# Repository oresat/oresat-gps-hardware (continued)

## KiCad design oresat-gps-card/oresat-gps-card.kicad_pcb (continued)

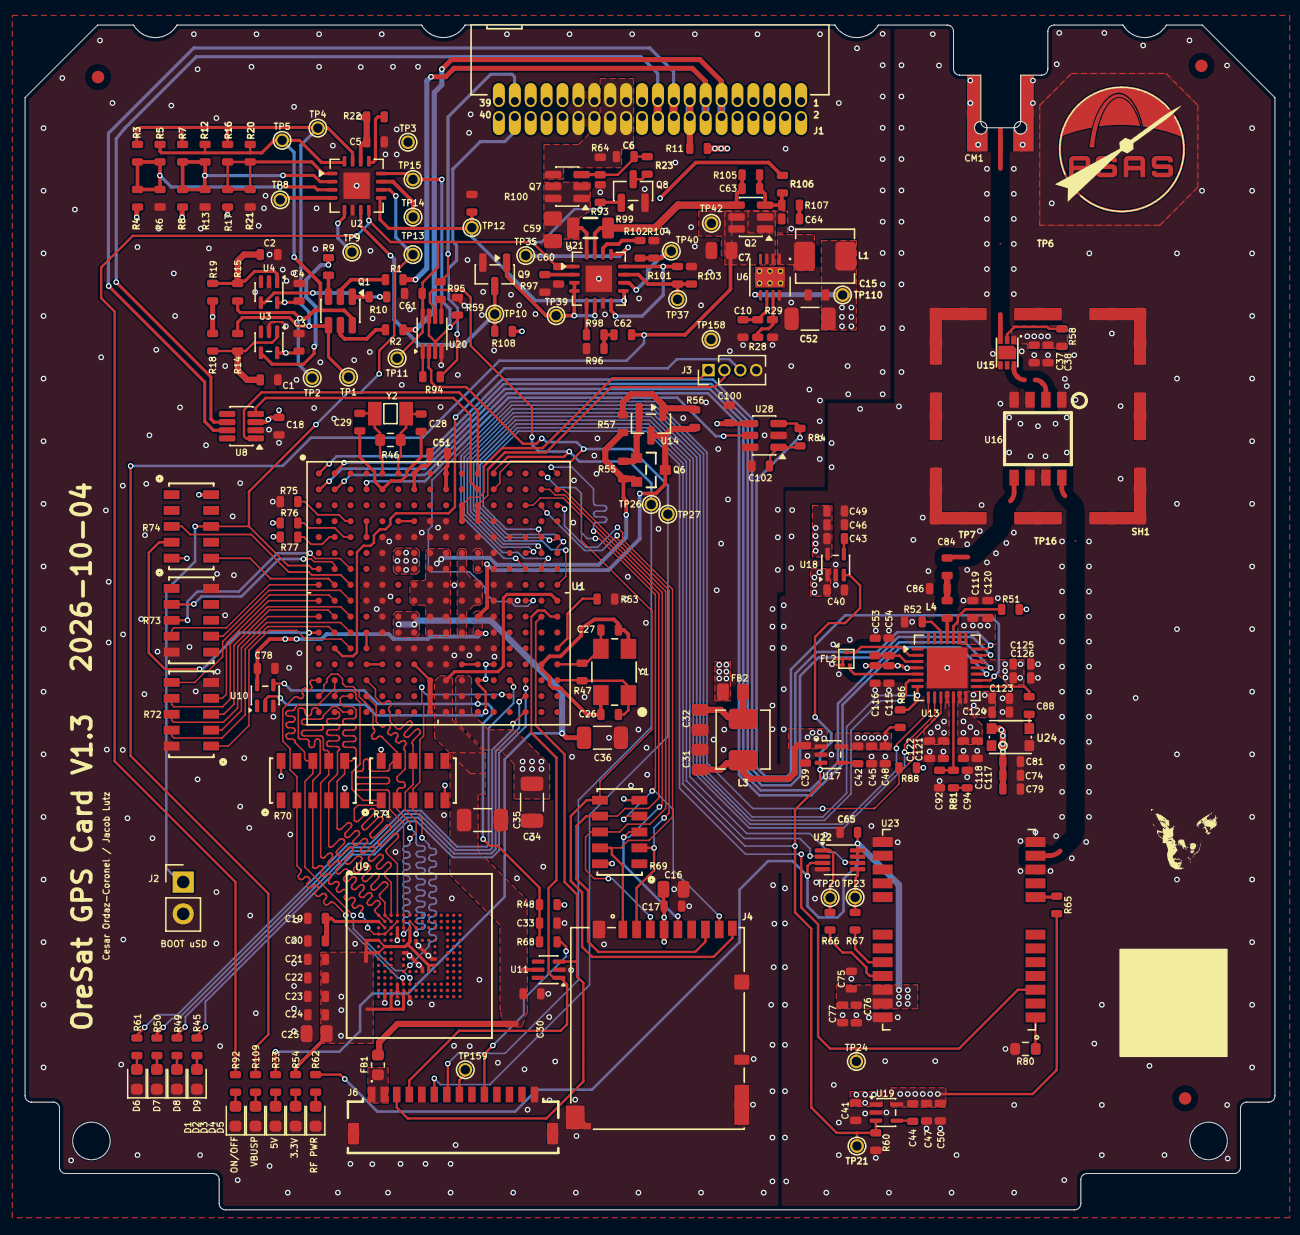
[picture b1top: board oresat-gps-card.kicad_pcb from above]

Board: 4 copper layers, 99.8 x 94.6 mm, 249 parts (0 on the bottom side), 188 nets.

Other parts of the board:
LOGO1: PSAS_LOGO_10X10

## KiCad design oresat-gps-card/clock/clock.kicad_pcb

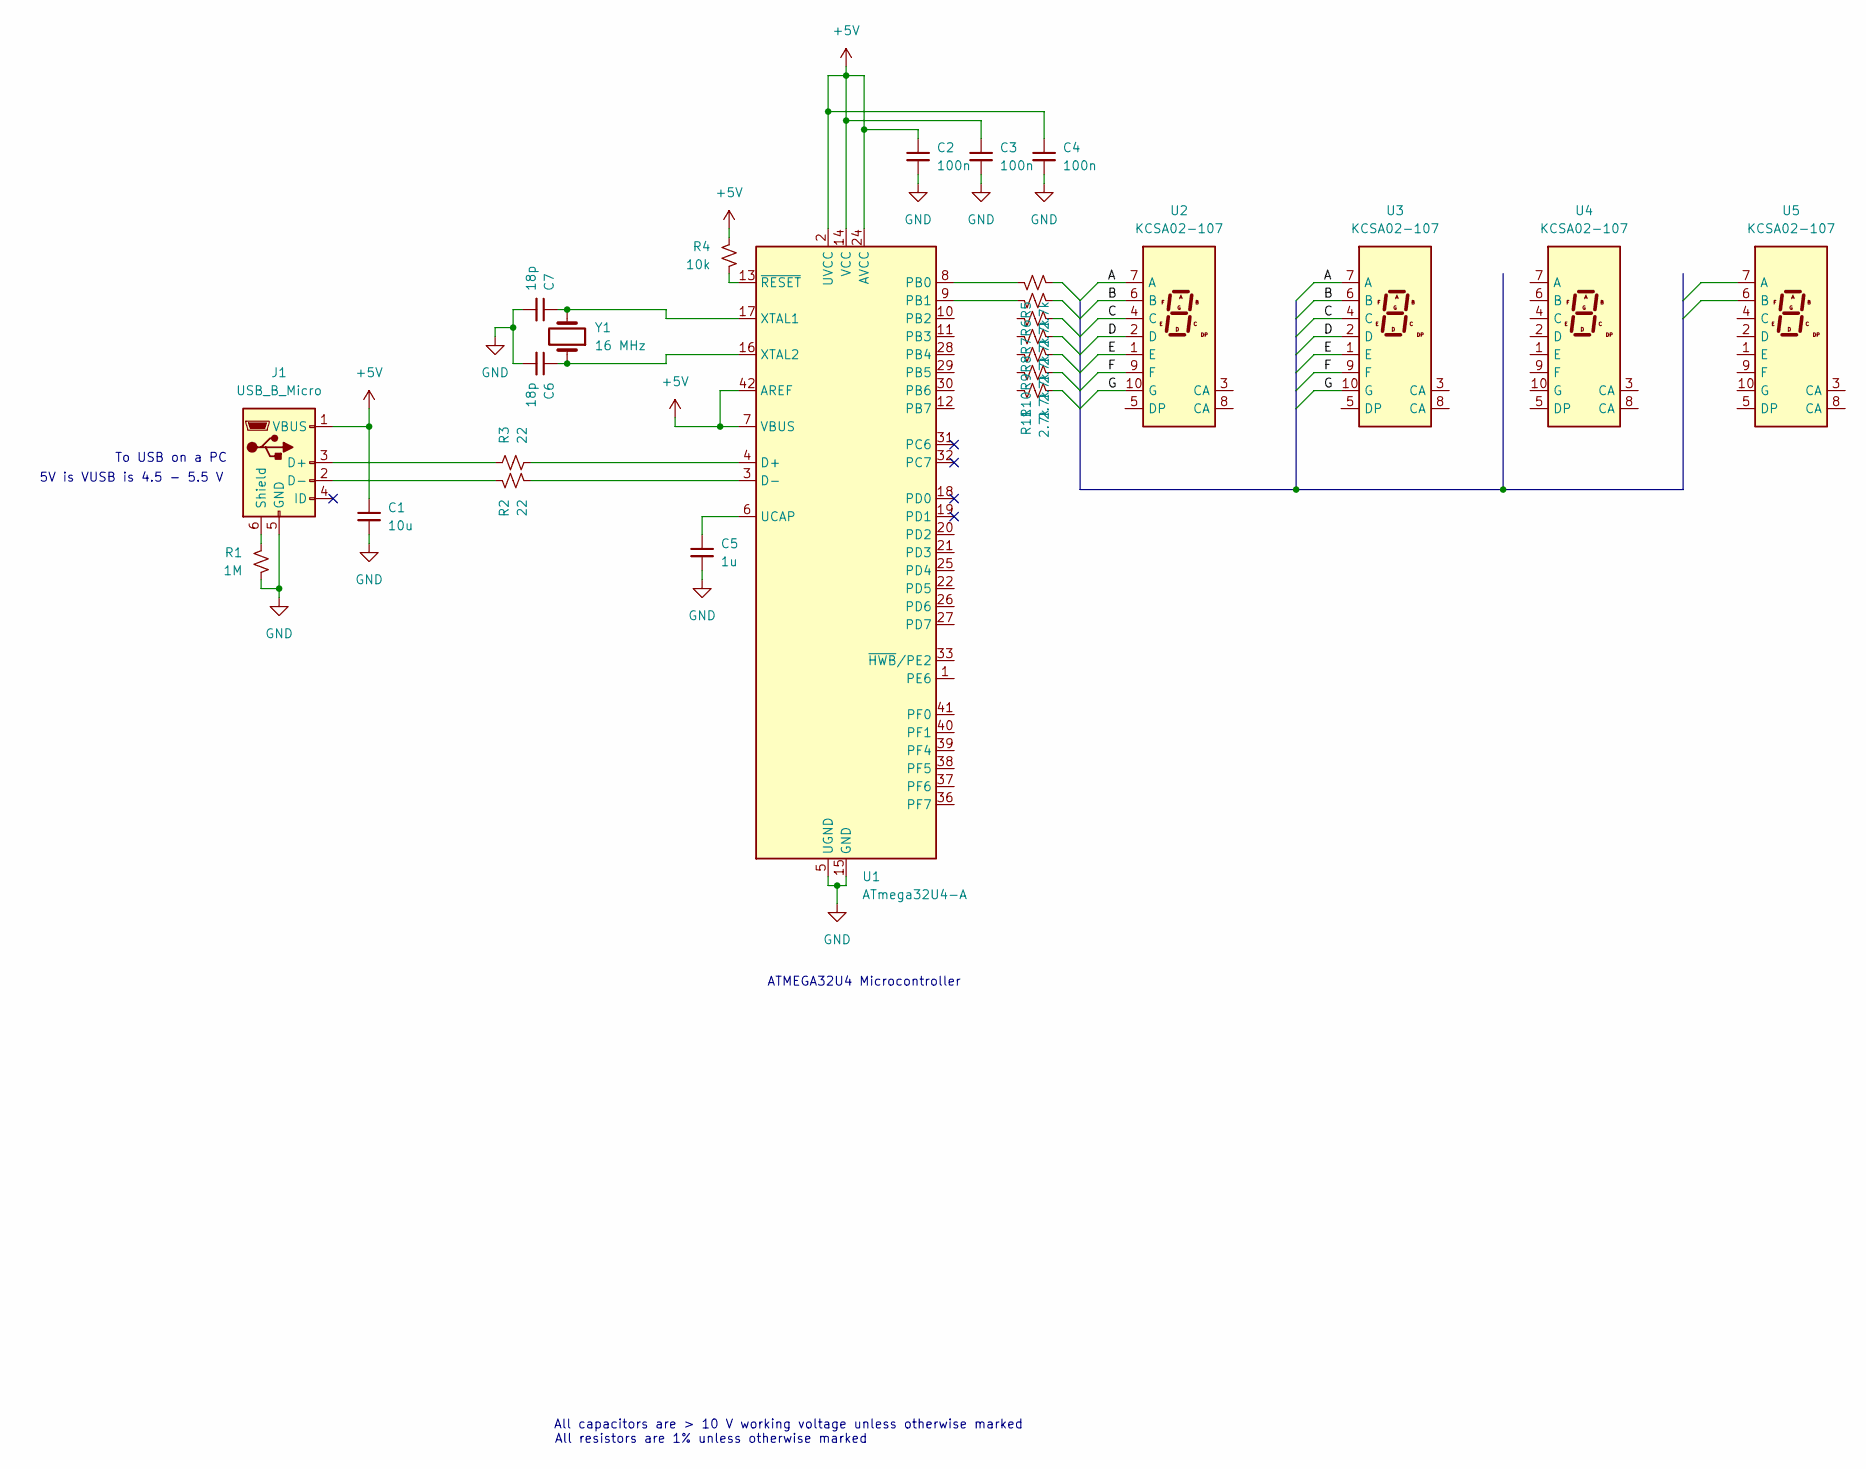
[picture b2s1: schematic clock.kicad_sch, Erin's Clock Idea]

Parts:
C1: 10u; C_0805_2012Metric
C2, C3, C4: 100n; C_0805_2012Metric
C5: 1u; C_0805_2012Metric
C6, C7: 18p; C_0805_2012Metric
J1: USB_B_Micro; USB_Micro-B_GCT_USB3076-30-A
R1: 1M; R_0805_2012Metric
R2, R3: 22; R_0805_2012Metric
R4: 10k; R_0805_2012Metric
R5, R6, R7, R8, R9, R10, R11: 2.7k; R_0805_2012Metric
U1: ATmega32U4-A; TQFP-44_10x10mm_P0.8mm
U2, U3, U4, U5: KCSA02-107; KCSC02-107
Y1: 16 MHz; Crystal_SMD_2012-2Pin_2.0x1.2mm

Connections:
+5V: C1.1, C2.1, C3.1, C4.1, J1.1 (VBUS), R4.1, U1.2 (UVCC), U1.7 (VBUS), U1.14 (VCC), U1.24 (AVCC), U1.34 (VCC), U1.42 (AREF), U1.44 (AVCC)
/A: U2.7 (A), U3.7 (A)
/B: U2.6 (B), U3.6 (B)
/C: U2.4 (C), U3.4 (C)
/D: U2.2 (D), U3.2 (D)
/E: U2.1 (E), U3.1 (E)
/F: U2.9 (F), U3.9 (F)
/G: U2.10 (G), U3.10 (G)
GND: C1.2, C2.2, C3.2, C4.2, C5.2, C6.2, C7.2, J1.5 (GND), R1.2, U1.5 (UGND), U1.15 (GND), U1.23 (GND), U1.35 (GND), U1.43 (GND)
unnamed: J1.3 (D+), R3.1
unnamed: J1.2 (D-), R2.1
unnamed: J1.6 (Shield), R1.1
unnamed: R3.2, U1.4 (D+)
unnamed: R2.2, U1.3 (D-)
unnamed: R5.1, U1.8 (PB0)
unnamed: R6.1, U1.9 (PB1)
unnamed: C5.1, U1.6 (UCAP)
unnamed: C7.1, U1.17 (XTAL1), Y1.2
unnamed: C6.1, U1.16 (XTAL2), Y1.1
unnamed: R4.2, U1.13 (~RESET)

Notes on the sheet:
5V is VUSB is 4.5 - 5.5 V
To USB on a PC
ATMEGA32U4 Microcontroller
All capacitors are > 10 V working voltage unless otherwise marked
All resistors are 1% unless otherwise marked

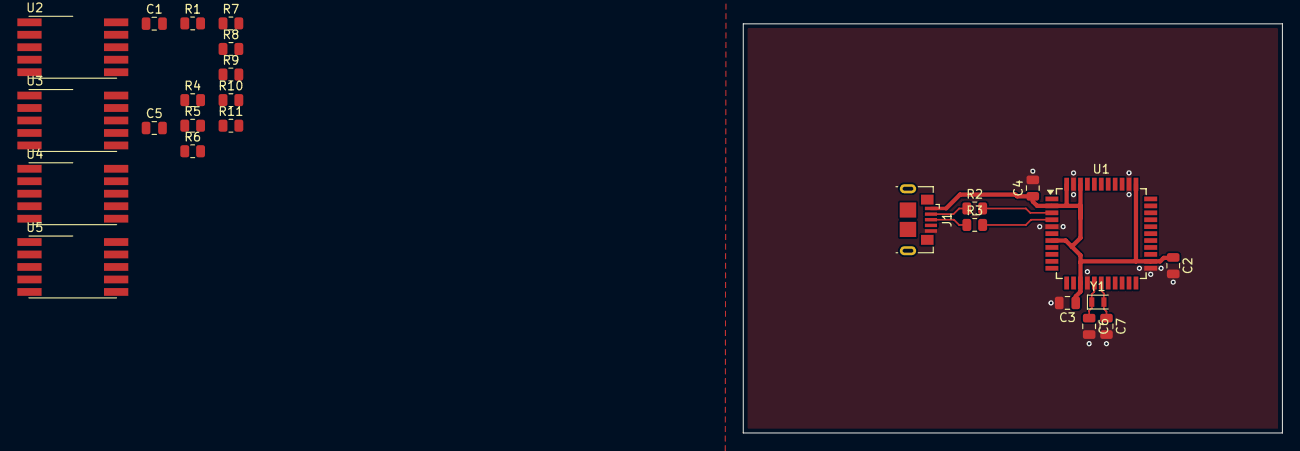
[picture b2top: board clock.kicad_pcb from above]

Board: 2 copper layers, 62.2 x 47.2 mm, 25 parts (0 on the bottom side), 20 nets.

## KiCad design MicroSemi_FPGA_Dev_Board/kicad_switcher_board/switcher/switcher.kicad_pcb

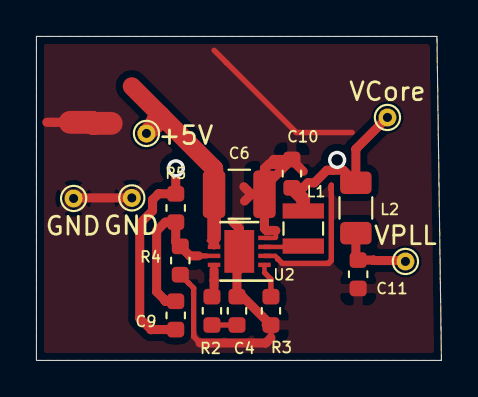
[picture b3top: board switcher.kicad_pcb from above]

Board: 4 copper layers, 22.5 x 18.0 mm, 17 parts (0 on the bottom side), 9 nets.

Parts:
+5V: +5V; TestPoint_THTPad_D1.0mm_Drill0.5mm
C4: 680pF; C_0603_1608Metric
C6: 22uF; C_1210_3225Metric
C9: 22pF; C_0603_1608Metric
C10, C11: 10uF; C_0603_1608Metric
GND: GND; TestPoint_THTPad_D1.0mm_Drill0.5mm
GND#2: GND; TestPoint_THTPad_D1.0mm_Drill0.5mm
L1: 2.2uH; L_Wuerth_MAPI-2512
L2: 6.8uH; L_1206_3216Metric
R2: 16.9K; R_0603_1608Metric
R3: 549K; R_0603_1608Metric
R4: 287K; R_0603_1608Metric
R5: 249K; R_0603_1608Metric
U2: LTC3561A; DFN-8-1EP_3x3mm_P0.5mm_EP1.66x2.38mm
VCore: 1.5V Core; TestPoint_THTPad_D1.0mm_Drill0.5mm
VPLL: 1.5V PLL; TestPoint_THTPad_D1.0mm_Drill0.5mm

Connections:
+5V: +5V.1, C6.1, U2.5, U2.6
GND: C4.2, C6.2, C10.2, C11.2, GND.1, GND#2.1, R3.1, R4.1, U2.2, U2.4, U2.9
unnamed: C4.1, R2.1
unnamed: C9.2, R4.2, R5.2, U2.7
unnamed: C9.1, C10.1, L1.2, L2.1, R5.1, VCore.1
unnamed: C11.1, L2.2, VPLL.1
unnamed: L1.1, U2.3
unnamed: R2.2, U2.8
unnamed: R3.2, U2.1

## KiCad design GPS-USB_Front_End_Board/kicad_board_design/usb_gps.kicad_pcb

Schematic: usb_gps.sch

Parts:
P1: CONN_02X12; Pin_Header_Straight_2x12; MPN SFH11-PBPC-D12-ST-BK

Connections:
/MAX_2769/+5V: P1.1, P1.2; also elsewhere on the board
/MAX_2769/D0: P1.10; also elsewhere on the board
/MAX_2769/D1: P1.12; also elsewhere on the board
/MAX_2769/D2: P1.14; also elsewhere on the board
/MAX_2769/D3: P1.16; also elsewhere on the board
/MAX_2769/LD: P1.6; also elsewhere on the board
/MAX_2769/SCLK: P1.22; also elsewhere on the board
/MAX_2769/SCS: P1.28; also elsewhere on the board
/MAX_2769/SDO: P1.26; also elsewhere on the board
/MAX_2769/SHDN#: P1.8; also elsewhere on the board
/MAX_2769/WR#: P1.20; also elsewhere on the board
/USB_FT2232/D0: P1.11; also elsewhere on the board
/USB_FT2232/D1: P1.9; also elsewhere on the board
/USB_FT2232/D2: P1.13; also elsewhere on the board
/USB_FT2232/D3: P1.15; also elsewhere on the board
/USB_FT2232/GPIO0: P1.7; also elsewhere on the board
/USB_FT2232/GPIO1: P1.5; also elsewhere on the board
/USB_FT2232/SCLK: P1.21; also elsewhere on the board
/USB_FT2232/SCS: P1.27; also elsewhere on the board
/USB_FT2232/SDI: P1.23; also elsewhere on the board
/USB_FT2232/SDO: P1.25; also elsewhere on the board
/USB_FT2232/TXE#: P1.17; also elsewhere on the board
/USB_FT2232/WR#: P1.19; also elsewhere on the board
GND: P1.3, P1.4; also elsewhere on the board

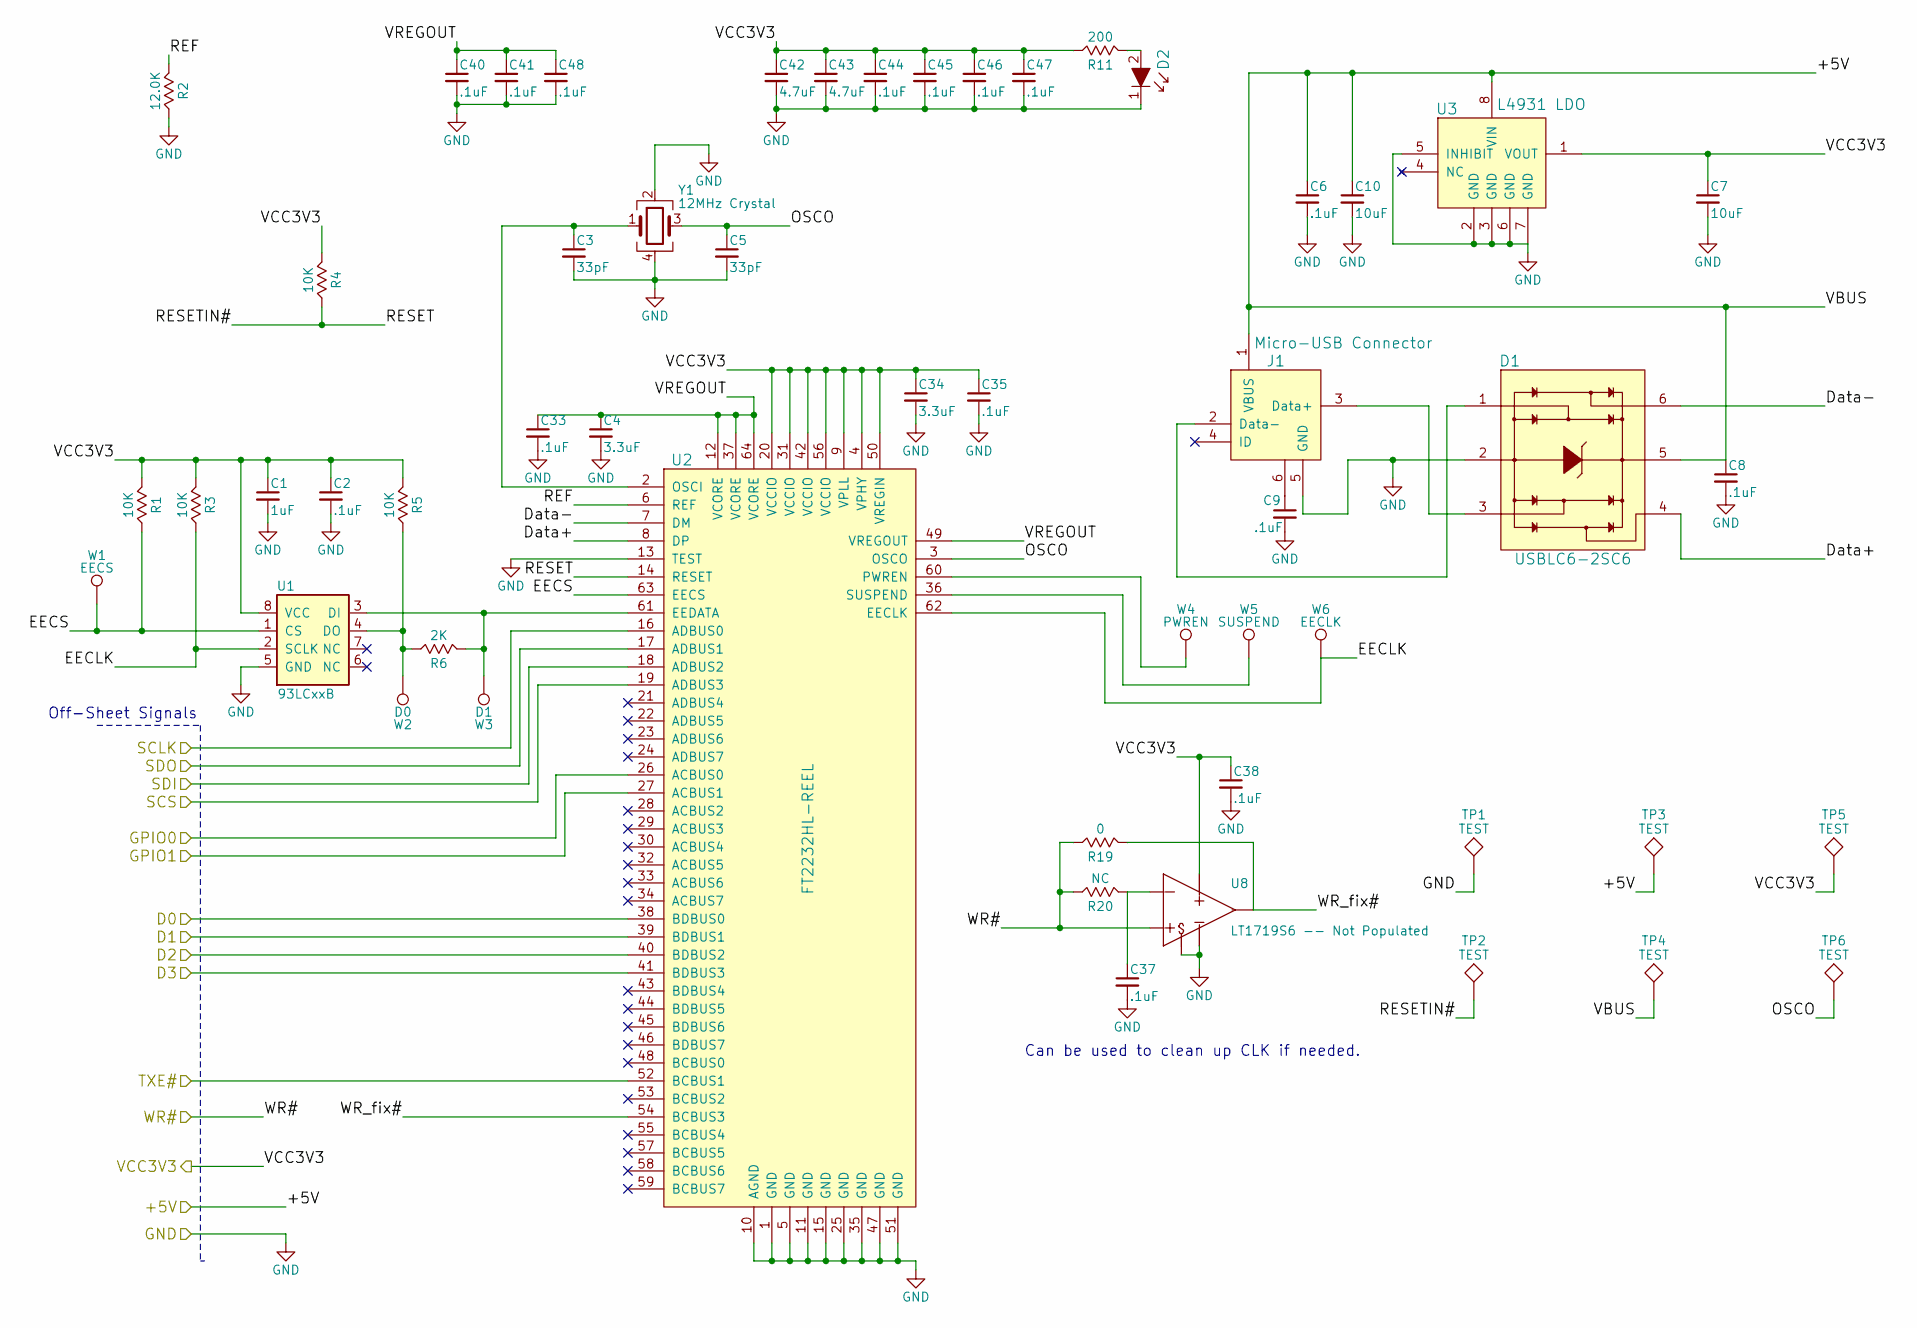
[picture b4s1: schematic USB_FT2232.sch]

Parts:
C1: 1uF; C_0603_HandSoldering; MPN CL10B105KP8NNNC
C2, C6, C8, C9, C33, C35, C37, C38, C40, C41, C44, C45, C46, C47, C48: .1uF; C_0402; MPN CGA2B1X7R1C104K050BC
C3, C5: 33pF; C_0805_HandSoldering; MPN C0805C330J5GACTU
C4, C34: 3.3uF; C_0402; MPN C1005X5R0J335K050BC
C7: 10uF; C_0805; MPN CL21A106KPFNNNG
C10: 10uF; C_0603_HandSoldering; MPN CL10B106MQ8NRNC
C42, C43: 4.7uF; C_0402; MPN LMF105B7472KVHF
D1: USBLC6-2SC6; SOT23-6L; MPN USBLC6-2SC6; Digi-Key_PN 497-5235-1-ND
D2: LTST-C171KRKT; 0805; MPN LTST-C171KRKT; Digi-Key_PN 160-1427-1-ND
J1: Micro-USB Connector; USB_Micro_B_Female_10118194-0001LF; MPN 10118194-0001LF; Digi-Key_PN 609-4618-6-ND
R1, R3, R4, R5: 10K; R_0805_HandSoldering; MPN CRGH0805F10K
R2: 12.0K; R_0603_HandSoldering; MPN CPF0603B12KE1
R6: 2K; R_0603_HandSoldering; MPN AC0603FR-072KL
R11: 200; 0805; MPN RR1220P-201-D
R19: 0; R_0603_HandSoldering; MPN CRCW06030000Z0EBC
R20: NC; R_0603_HandSoldering; MPN CRCW06030000Z0EBC
TP1: TEST; Test_Point
TP2, TP3, TP4, TP5, TP6: TEST; Measurement_Point_Round-TH_Small
U1: 93LCxxB; SOIC127P600X175-8N; MPN 93LC46B-I/SN
U2: FT2232HL-REEL; LQFP-64_10x10mm; MPN FT2232HL-REEL; Digi-Key_PN 768-1024-1-ND
U3: L4931 LDO; SOIC-8_W3.9mm; MPN L4931ABD33-TR; Digi-Key_PN 497-1155-1-ND
U8: LT1719S6 -- Not Populated; TSOT-23_S6; MPN LT1719IS6#TRMPBF
W1: EECS; Measurement_Point_Round-TH_Small
W2: D0; Measurement_Point_Round-TH_Small
W3: D1; Measurement_Point_Round-TH_Small
W4: PWREN; Measurement_Point_Round-TH_Small
W5: SUSPEND; Measurement_Point_Round-TH_Small
W6: EECLK; Measurement_Point_Round-TH_Small
Y1: 12MHz Crystal; CTS_405_xtal; MPN 405C35E12M00000

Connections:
/MAX_2769/+5V: C6.1, C8.1, C10.1, D1.5, J1.1 (VBUS), TP3.1, TP4.1, U3.8 (VIN); also elsewhere on the board
/MAX_2769/VCC3V3: C1.1, C2.1, C7.1, C34.1, C35.1, C38.1, C42.1, C43.1, C44.1, C45.1, C46.1, C47.1, R1.1, R3.1, R4.1, R5.1, R11.2, TP5.1, U1.8 (VCC), U2.4 (VPHY), U2.9 (VPLL), U2.20 (VCCIO), U2.31 (VCCIO), U2.42 (VCCIO), U2.50 (VREGIN), U2.56 (VCCIO), U3.1 (VOUT), U8.4 (V+); also elsewhere on the board
/USB_FT2232/D0: U2.38 (BDBUS0); also elsewhere on the board
/USB_FT2232/D1: U2.39 (BDBUS1); also elsewhere on the board
/USB_FT2232/D2: U2.40 (BDBUS2); also elsewhere on the board
/USB_FT2232/D3: U2.41 (BDBUS3); also elsewhere on the board
/USB_FT2232/Data+: D1.4, U2.8 (DP)
/USB_FT2232/Data-: D1.6, U2.7 (DM)
/USB_FT2232/EECLK: R3.2, U1.2 (SCLK), U2.62 (EECLK), W6.1
/USB_FT2232/EECS: R1.2, U1.1 (CS), U2.63 (EECS), W1.1
/USB_FT2232/GPIO0: U2.26 (ACBUS0); also elsewhere on the board
/USB_FT2232/GPIO1: U2.27 (ACBUS1); also elsewhere on the board
/USB_FT2232/OSCO: C5.1, TP6.1, U2.3 (OSCO), Y1.3
/USB_FT2232/REF: R2.1, U2.6 (REF)
/USB_FT2232/RESET: R4.2, TP2.1, U2.14 (RESET)
/USB_FT2232/SCLK: U2.16 (ADBUS0); also elsewhere on the board
/USB_FT2232/SCS: U2.19 (ADBUS3); also elsewhere on the board
/USB_FT2232/SDI: U2.18 (ADBUS2); also elsewhere on the board
/USB_FT2232/SDO: U2.17 (ADBUS1); also elsewhere on the board
/USB_FT2232/TXE#: U2.52 (BCBUS1); also elsewhere on the board
/USB_FT2232/VREGOUT: C4.1, C33.1, C40.1, C41.1, C48.1, U2.12 (VCORE), U2.37 (VCORE), U2.49 (VREGOUT), U2.64 (VCORE)
/USB_FT2232/WR#: R19.2, R20.2, U8.3 (IN+); also elsewhere on the board
/USB_FT2232/WR_fix#: R19.1, U2.54 (BCBUS3), U8.5 (OUT)
GND: C1.2, C2.2, C3.2, C4.2, C5.2, C6.2, C7.2, C8.2, C9.2, C10.2, C33.2, C34.2, C35.2, C37.2, C38.2, C40.2, C41.2, C42.2, C43.2, C44.2, C45.2, C46.2, C47.2, C48.2, D1.2, D2.1, J1.5 (GND), R2.2, TP1.1, U1.5 (GND), U2.1 (GND), U2.5 (GND), U2.10 (AGND), U2.11 (GND), U2.13 (TEST), U2.15 (GND), U2.25 (GND), U2.35 (GND), U2.47 (GND), U2.51 (GND), U3.2 (GND), U3.3 (GND), U3.5 (INHIBIT), U3.6 (GND), U3.7 (GND), U8.2 (V-), U8.6 (SHDN), Y1.2, Y1.4; also elsewhere on the board
unnamed: C3.1, U2.2 (OSCI), Y1.1
unnamed: C9.1, J1.6
unnamed: C37.1, R20.1, U8.1 (IN)
unnamed: D1.1, J1.2 (Data-)
unnamed: D1.3, J1.3 (Data+)
unnamed: D2.2, R11.1
unnamed: R5.2, R6.2, U1.4 (DO), W2.1
unnamed: R6.1, U1.3 (DI), U2.61 (EEDATA), W3.1
unnamed: U2.36 (SUSPEND), W5.1
unnamed: U2.60 (PWREN), W4.1

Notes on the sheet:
Off-Sheet Signals
Can be used to clean up CLK if needed.

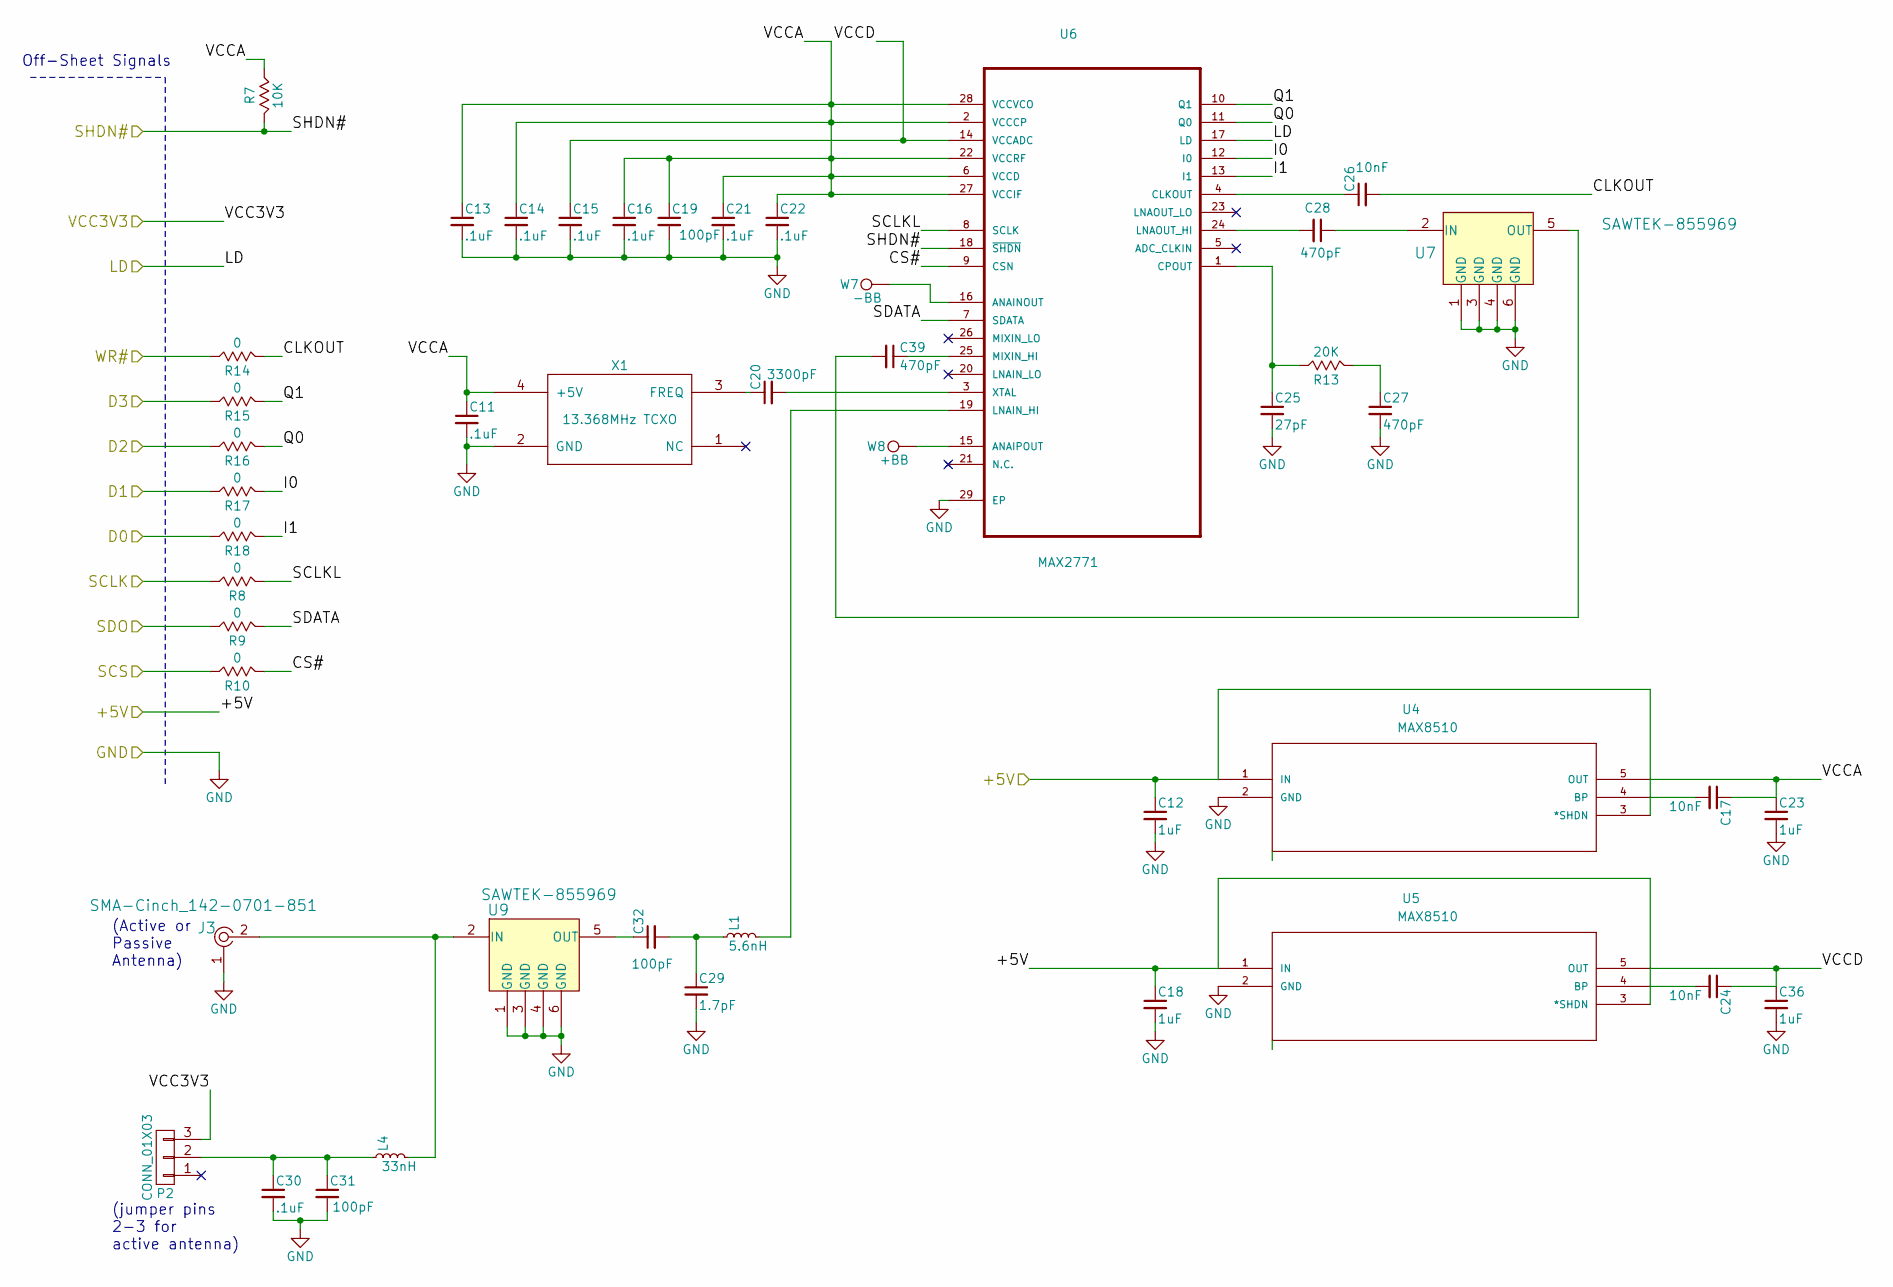
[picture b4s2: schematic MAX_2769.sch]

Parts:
C11, C13, C14, C15, C16, C21, C22, C30: .1uF; C_0402; MPN CGA2B1X7R1C104K050BC
C12, C18: 1uF; C_0603_HandSoldering; MPN CL10B105KP8NNNC
C17, C24, C26: 10nF; C_0402; MPN GRM155R71C103KA01D
C19, C31, C32: 100pF; C_0402; MPN CC0402JRNPO9BN101
C20: 3300pF; C_0603_HandSoldering; MPN 06035C332KAT4A
C23, C36: 1uF; C_0805; MPN C0805C105K4RACTU
C25: 27pF; C_0805_HandSoldering; MPN 08055C270KAT2A
C27, C28, C39: 470pF; C_0402; MPN 04025C471KAT2A
C29: 1.7pF; C_0402; MPN GJM1555C1H1R7WB01D
J3: SMA-Cinch_142-0701-851; Cinch_142-0701-851; MPN 5-1814832-1; Digi-Key_PN A97594-ND
L1: 5.6nH; C_0402; MPN L-07C5N6SV6T
L4: 33nH; C_0402; MPN CI100505-33NJ
P2: CONN_01X03; Molex_KK-6410-03_03x2.54mm_Straight; MPN PREC003SAAN-RC
R7: 10K; R_0805_HandSoldering; MPN CRGH0805F10K
R8, R9, R10, R14, R15, R16, R17, R18: 0; R_0805_HandSoldering; MPN CRCW06030000Z0EBC
R13: 20K; R_0603_HandSoldering; MPN CRT0603-FZ-2002EST
U4, U5: MAX8510; 21-0076E_FLIP; MPN MAX8510EXK30+T
U6: MAX2771; TQFP_29_EP_MAX2769; MPN MAX2771ETI+
U7, U9: SAWTEK-855969; Sawtek_855969; MPN 855969; Digi-Key_PN AP2114H-3.3TRG1DICT-ND
W7: -BB; Measurement_Point_Round-TH_Small
W8: +BB; Measurement_Point_Round-TH_Small
X1: 13.368MHz TCXO; TCXO_Taitien; MPN TXETCDSANF-16.368000

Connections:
/MAX_2769/+5V: C12.1, C18.1, U4.1 (IN), U4.3 (*SHDN), U5.1 (IN), U5.3 (*SHDN); also elsewhere on the board
/MAX_2769/CLKOUT: C26.2, R14.1
/MAX_2769/CS#: R10.1, U6.9 (CSN)
/MAX_2769/D0: R18.2; also elsewhere on the board
/MAX_2769/D1: R17.2; also elsewhere on the board
/MAX_2769/D2: R16.2; also elsewhere on the board
/MAX_2769/D3: R15.2; also elsewhere on the board
/MAX_2769/I0: R17.1, U6.12 (I0)
/MAX_2769/I1: R18.1, U6.13 (I1)
/MAX_2769/LD: U6.17 (LD); also elsewhere on the board
/MAX_2769/Q0: R16.1, U6.11 (Q0)
/MAX_2769/Q1: R15.1, U6.10 (Q1)
/MAX_2769/SCLK: R8.2; also elsewhere on the board
/MAX_2769/SCLKL: R8.1, U6.8 (SCLK)
/MAX_2769/SCS: R10.2; also elsewhere on the board
/MAX_2769/SDATA: R9.1, U6.7 (SDATA)
/MAX_2769/SDO: R9.2; also elsewhere on the board
/MAX_2769/SHDN#: R7.1, U6.18 (~SHDN); also elsewhere on the board
/MAX_2769/VCC3V3: P2.3; also elsewhere on the board
/MAX_2769/VCCA: C11.1, C13.1, C14.1, C16.1, C17.1, C19.1, C21.1, C22.1, C23.1, R7.2, U4.5 (OUT), U6.2 (VCCCP), U6.6 (VCCD), U6.22 (VCCRF), U6.27 (VCCIF), U6.28 (VCCVCO), X1.4 (+5V)
/MAX_2769/VCCD: C15.1, C24.1, C36.1, U5.5 (OUT), U6.14 (VCCADC)
/MAX_2769/WR#: R14.2; also elsewhere on the board
GND: C11.2, C12.2, C13.2, C14.2, C15.2, C16.2, C18.2, C19.2, C21.2, C22.2, C23.2, C25.2, C27.2, C29.2, C30.2, C31.2, C36.2, J3.1, U4.2 (GND), U5.2 (GND), U6.29 (EP), U7.1 (GND), U7.3 (GND), U7.4 (GND), U7.6 (GND), U9.1 (GND), U9.3 (GND), U9.4 (GND), U9.6 (GND), X1.2 (GND); also elsewhere on the board
unnamed: C17.2, U4.4 (BP)
unnamed: C20.1, X1.3 (FREQ)
unnamed: C20.2, U6.3 (XTAL)
unnamed: C24.2, U5.4 (BP)
unnamed: C25.1, R13.2, U6.1 (CPOUT)
unnamed: C26.1, U6.4 (CLKOUT)
unnamed: C27.1, R13.1
unnamed: C28.1, U7.2 (IN)
unnamed: C28.2, U6.24 (LNAOUT_HI)
unnamed: C29.1, C32.2, L1.1
unnamed: C30.1, C31.1, L4.1, P2.2
unnamed: C32.1, U9.5 (OUT)
unnamed: C39.1, U6.25 (MIXIN_HI)
unnamed: C39.2, U7.5 (OUT)
unnamed: J3.2, L4.2, U9.2 (IN)
unnamed: L1.2, U6.19 (LNAIN_HI)
unnamed: U6.15 (ANAIPOUT), W8.1
unnamed: U6.16 (ANAINOUT), W7.1

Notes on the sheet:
(Active or Passive Antenna)
Off-Sheet Signals
(jumper pins 2-3 for active antenna)

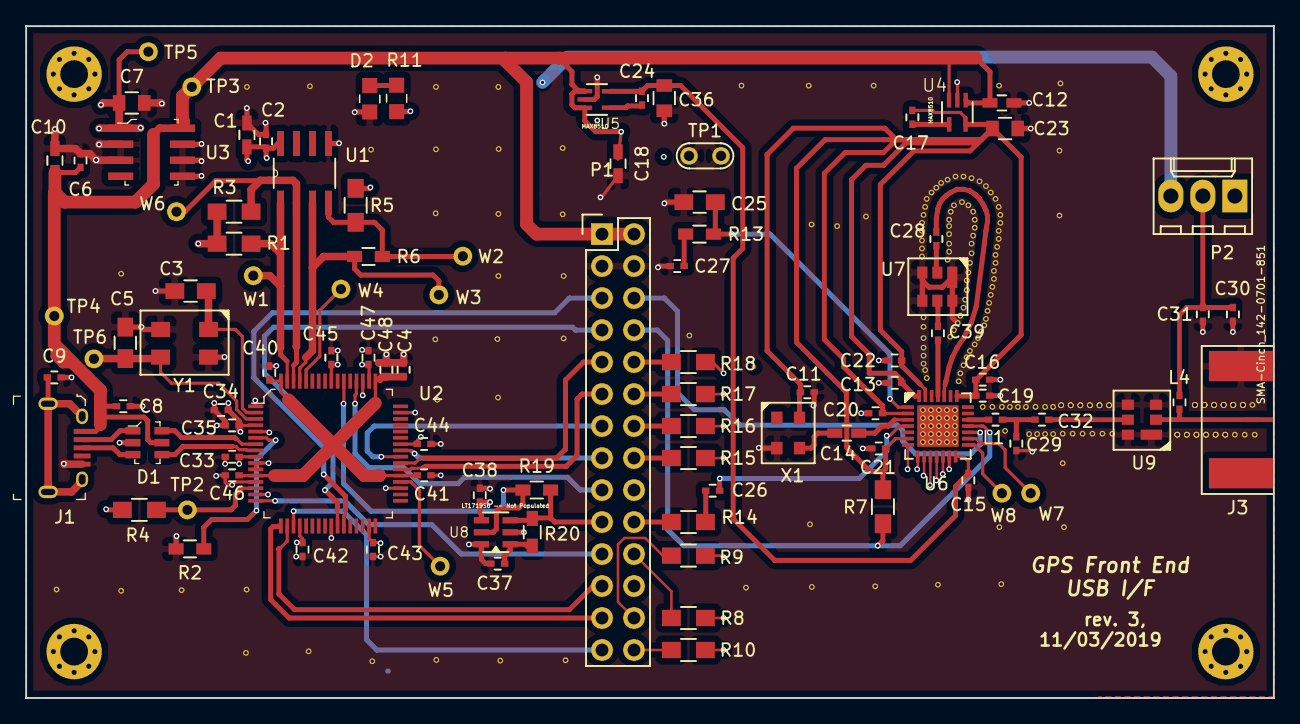
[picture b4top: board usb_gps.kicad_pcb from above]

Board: 4 copper layers, 99.1 x 53.3 mm, 100 parts (0 on the bottom side), 72 nets.

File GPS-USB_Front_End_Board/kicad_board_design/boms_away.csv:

Refs,Value,Footprint,Quantity,MFR,MPN,SPR,SPN
C8;C6;C2;C35;C33;C9;C11;C13;C14;C15;C16;C21;C22;C30;C38;C37,.1uF,Capacitors_SMD:C_0402,16,TDK,CGA2B1X7R1C104K050BC,Digikey,445-5613-1-ND
C29,1.7pF,Capacitors_SMD:C_0402,1,Murata,GJM1555C1H1R7WB01D,Digikey,490-11201-1-ND
C32;C31;C19,100pF,Capacitors_SMD:C_0402,3,Yageo,CC0402JRNPO9BN101,Digikey,311-1024-1-ND
C26;C24;C17,10nF,Capacitors_SMD:C_0402,3,Murata,GRM155R71C103KA01D,Digikey,490-1313-1-ND
L4,33nH,Capacitors_SMD:C_0402,1,Bourns,CI100505-33NJ,Digikey,CI100505-33NJCT-ND
C27;C39;C28,470pF,Capacitors_SMD:C_0402,3,AVX,04025C471KAT2A,Digikey,478-1097-1-ND
L1,5.6nH,Capacitors_SMD:C_0402,1,Johansen Technology,L-07C5N6SV6T,Digikey,712-1462-1-ND
C10,10uF,Capacitors_SMD:C_0603_HandSoldering,1,Samsung,CL10B106MQ8NRNC,Digikey,1276-1948-1-ND
C1;C12;C18,1uF,Capacitors_SMD:C_0603_HandSoldering,3,Samsung,CL10B105KP8NNNC,Digikey,1276-1946-1-ND
C20,3300pF,Capacitors_SMD:C_0603_HandSoldering,1,AVX,06035C332KAT4A,Digikey,478-10681-1-ND
C7;C23;C36,10uF,Capacitors_SMD:C_0805,3,Samsung,CL21A106KPFNNNG,Digikey,1276-6456-1-ND
C5;C3,10pF,Capacitors_SMD:C_0805_HandSoldering,2,Kemet,C0805C100K5RAC7800,Digikey,399-17612-1-ND
C25,27pF,Capacitors_SMD:C_0805_HandSoldering,1,AVX,08055C270KAT2A,Digikey,478-11394-1-ND
C4;C34,3.3uF,Capacitors_SMD:C_0805_HandSoldering,2,TDK,C2012X7R1C335K125AB,Digikey,445-7582-1-ND
P2,CONN_01X03,Connectors_Molex:Molex_KK-6410-03_03x2.54mm_Straight,1,Sullins,PREC003SAAN-RC,Digikey,S1012EC-03-ND
W8,+BB,Measurement_Points:Measurement_Point_Round-TH_Small,1,-,-,-,-
W7,-BB,Measurement_Points:Measurement_Point_Round-TH_Small,1,-,-,-,-
W2,D0,Measurement_Points:Measurement_Point_Round-TH_Small,1,-,-,-,-
W3,D1,Measurement_Points:Measurement_Point_Round-TH_Small,1,-,-,-,-
W6,EECLK,Measurement_Points:Measurement_Point_Round-TH_Small,1,-,-,-,-
W1,EECS,Measurement_Points:Measurement_Point_Round-TH_Small,1,-,-,-,-
W4,PWREN,Measurement_Points:Measurement_Point_Round-TH_Small,1,-,-,-,-
W5,SUSPEND,Measurement_Points:Measurement_Point_Round-TH_Small,1,-,-,-,-
TP3;TP5;TP6;TP4;TP2,TEST,Measurement_Points:Measurement_Point_Round-TH_Small,5,-,-,-,-
TP1,TEST,Measurement_Points:Test_Point,1,-,-,-,-
P1,CONN_02X12,Pin_Headers:Pin_Header_Straight_2x12,1,Sullins,SFH11-PBPC-D12-ST-BK,Digikey,S9708-ND
R19,0,Resistors_SMD:R_0603_HandSoldering,1,Vishay,CRCW06030000Z0EBC,Digikey,541-4013-1-ND
R2,12.0K,Resistors_SMD:R_0603_HandSoldering,1,TE Connectivity,CPF0603B12KE1,Digikey,A103037CT-ND
R13,20K,Resistors_SMD:R_0603_HandSoldering,1,Bourns,CRT0603-FZ-2002EST,Digikey,CRT0603-FZ-2002ESTCT-ND
R6,2K,Resistors_SMD:R_0603_HandSoldering,1,Yageo,AC0603FR-072KL,Digikey,YAG3590CT-ND
R20,NC,Resistors_SMD:R_0603_HandSoldering,1,Vishay,CRCW06030000Z0EBC,Digikey,541-4013-1-ND
R15;R16;R17;R18;R14;R10;R9;R8,0,Resistors_SMD:R_0805_HandSoldering,8,Vishay,CRCW06030000Z0EBC,Digikey,541-4013-1-ND
R5;R3;R1;R4;R7,10K,Resistors_SMD:R_0805_HandSoldering,5,TE Connectivity,CRGH0805F10K,Digikey,A126417DKR-ND
FB1,BLM18PG471SN1D,digikey-footprints:0603,1,Taiyo Yuden,BK0603HS330-T,Digikey,587-1828-1-ND
U2,FT2232HL-REEL,digikey-footprints:LQFP-64_10x10mm,1,FTDI,FT2232HL-REEL,Digikey,768-1024-1-ND
J3,SMA,digikey-footprints:RF_SMA_Vertical_5-1814832-1,1,Linx Technologies,5-1814832-1,Digikey,CONSMA001-SMD-G-ND
U3,L4931 LDO,digikey-footprints:SOIC-8_W3.9mm,1,STMicro,L4931ABD33-TR,Digikey,497-1155-1-ND
D1,USBLC6-2SC6,digikey-footprints:SOT23-6L,1,STMicro,USBLC6-2SC6,Digikey,497-5235-1-ND
J1,Micro-USB Connector,digikey-footprints:USB_Micro_B_Female_10118194-0001LF,1,Amphenol,10118194-0001LF,Digikey,609-4613-1-ND
U1,93LCxxB,mem:SOIC127P600X175-8N,1,MicroChip,93LC46B-I/SN,Digikey,93LC46B-I/SN-ND
Y1,12MHz Crystal,oscillator:CTS_405_xtal,1,CTS,405C35E12M00000,Digikey,CTX819DKR-ND
U4;U5,MAX8510,rf:21-0076E_FLIP,2,Maxim,MAX8510EXK30+T,Digikey,MAX8510EXK30+TCT-ND
U7,SAWTEK-855969,rf:Sawtek_855969,1,Qorvo,855969,Mouser,772-855969
X1,13.368MHz TCXO,rf:TCXO_Taitien,1,Taitien,TXETCDSANF-16.368000,Digikey,1664-1271-1-ND
U6,MAX2771,rf:TQFP_29_EP_MAX2769,1,Maxim,MAX2771ETI+,Digikey,MAX2771ETI+-ND
U8,LT1719S6 -- Not Populated,rf:TSOT-23_S6,1,Linear Tech,LT1719IS6#TRMPBF,Digikey,LT1719IS6#TRMPBFCT-ND

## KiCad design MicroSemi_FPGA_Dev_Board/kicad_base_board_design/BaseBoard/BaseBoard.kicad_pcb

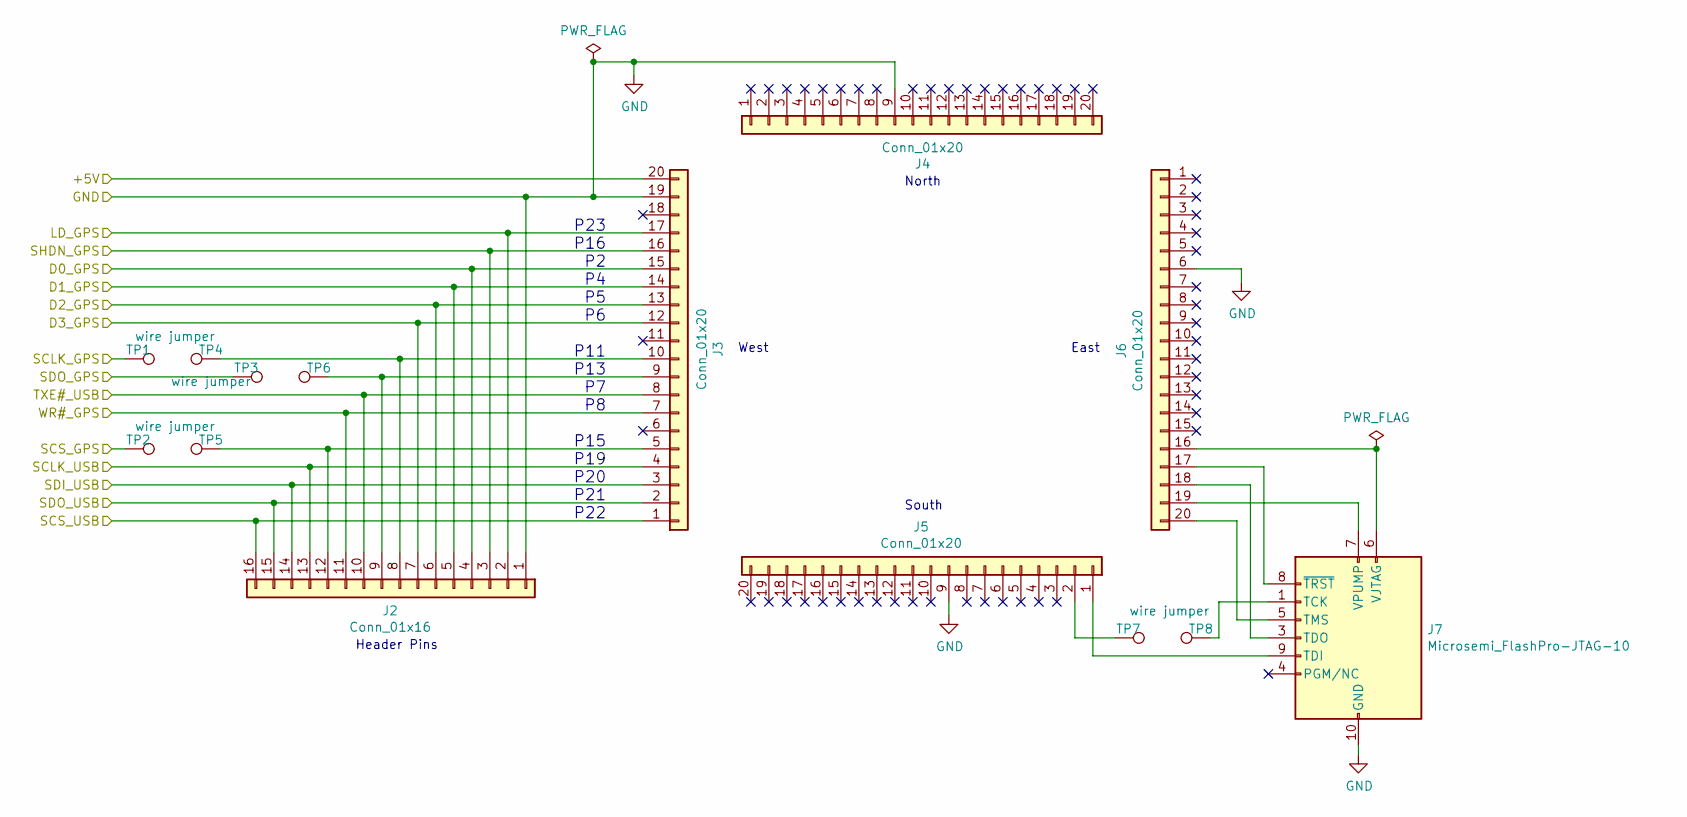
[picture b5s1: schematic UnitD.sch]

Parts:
J2: Conn_01x16; PinHeader_1x16_P2.54mm_Vertical
J3, J4, J5, J6: Conn_01x20; CastellatedPad20
J7: Microsemi_FlashPro-JTAG-10; IDC-Header_2x05_P2.54mm_Vertical
TP1, TP2, TP3, TP4, TP5, TP6, TP7, TP8: wire jumper; TestPoint_THTPad_D1.5mm_Drill0.7mm

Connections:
/Sheet5DD758E7/+5V: J3.20; also elsewhere on the board
/Sheet5DD758E7/D0_GPS: J2.4, J3.15; also elsewhere on the board
/Sheet5DD758E7/D1_GPS: J2.5, J3.14; also elsewhere on the board
/Sheet5DD758E7/D2_GPS: J2.6, J3.13; also elsewhere on the board
/Sheet5DD758E7/D3_GPS: J2.7, J3.12; also elsewhere on the board
/Sheet5DD758E7/LD_GPS: J2.2, J3.17; also elsewhere on the board
/Sheet5DD758E7/SCLK_GPS: TP1.1; also elsewhere on the board
/Sheet5DD758E7/SCLK_USB: J2.13, J3.4; also elsewhere on the board
/Sheet5DD758E7/SCS_GPS: TP2.1; also elsewhere on the board
/Sheet5DD758E7/SCS_USB: J2.16, J3.1; also elsewhere on the board
/Sheet5DD758E7/SDI_USB: J2.14, J3.3; also elsewhere on the board
/Sheet5DD758E7/SDO_GPS: TP3.1; also elsewhere on the board
/Sheet5DD758E7/SDO_USB: J2.15, J3.2; also elsewhere on the board
/Sheet5DD758E7/SHDN_GPS: J2.3, J3.16; also elsewhere on the board
/Sheet5DD758E7/TXE#_USB: J2.10, J3.8; also elsewhere on the board
/Sheet5DD758E7/WR#_GPS: J2.11, J3.7; also elsewhere on the board
GND: J2.1, J3.19, J4.9, J5.9, J6.6, J7.2 (GND), J7.10 (GND); also elsewhere on the board
unnamed: J2.8, J3.10, TP4.1
unnamed: J2.9, J3.9, TP6.1
unnamed: J2.12, J3.5, TP5.1
unnamed: J5.1, J7.9 (TDI)
unnamed: J5.2, TP7.1
unnamed: J6.16, J7.6 (VJTAG)
unnamed: J6.17, J7.8 (~TRST)
unnamed: J6.18, J7.3 (TDO)
unnamed: J6.19, J7.7 (VPUMP)
unnamed: J6.20, J7.5 (TMS)
unnamed: J7.1 (TCK), TP8.1

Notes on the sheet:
Header Pins
North
South
West
East
P23 P16 P2 P4 P5 P6 P11 P13 P7 P8 P15 P19 P20 P21 P22
